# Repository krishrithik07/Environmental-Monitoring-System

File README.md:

# Environmental Monitoring System

**ESP32-C3 | LoRa Communication | KiCad PCB Design**

## Project Overview

This project focuses on designing an IoT-based Environmental Monitoring System using an ESP32-C3 microcontroller and LoRa communication.

The system integrates multiple sensors to monitor environmental conditions, including gas leakage, temperature and flame detection.

## Hardware Components

| Component | Purpose |
|---|---|
| ESP32-C3 | Main Controller |
| LoRa RA-02 | Wireless Communication |
| MQ-2 | Gas Detection |
| MQ-4 | Methane Detection |
| MQ-7 | Carbon Monoxide Detection |
| Temperature Sensor | Temperature Monitoring |
| Flame Sensor | Flame Detection |
| LM2576T-5.0 | 5V Power Regulation |
| LM2576T-3.3 | 3.3V Power Regulation |

## Design Tools

- KiCad – Schematic Capture and PCB Design
- ESP32-C3 – Embedded Controller
- LoRa – Wireless Communication

## Project Architecture

The system consists of a main controller and multiple sensor nodes. Sensor data is collected and communicated wirelessly through LoRa.

## Design Progress

- [ ] Component selection
- [ ] Schematic design
- [ ] Electrical Rule Check (ERC)
- [ ] PCB footprint assignment
- [ ] PCB layout
- [ ] Design Rule Check (DRC)
- [ ] Gerber generation
- [ ] PCB fabrication and testing

## Repository Structure

- `Schematic/` – KiCad schematic files
- `PCB_Layout/` – PCB design files
- `Libraries/` – Custom symbols and footprints
- `Datasheets/` – Component datasheets
- `BOM/` – Bill of Materials
- `Manufacturing/` – Manufacturing output files

## Author

**Krishna Raj M**

Electronics and Communication Engineering

**Project Category:** Embedded Systems | IoT | PCB Design

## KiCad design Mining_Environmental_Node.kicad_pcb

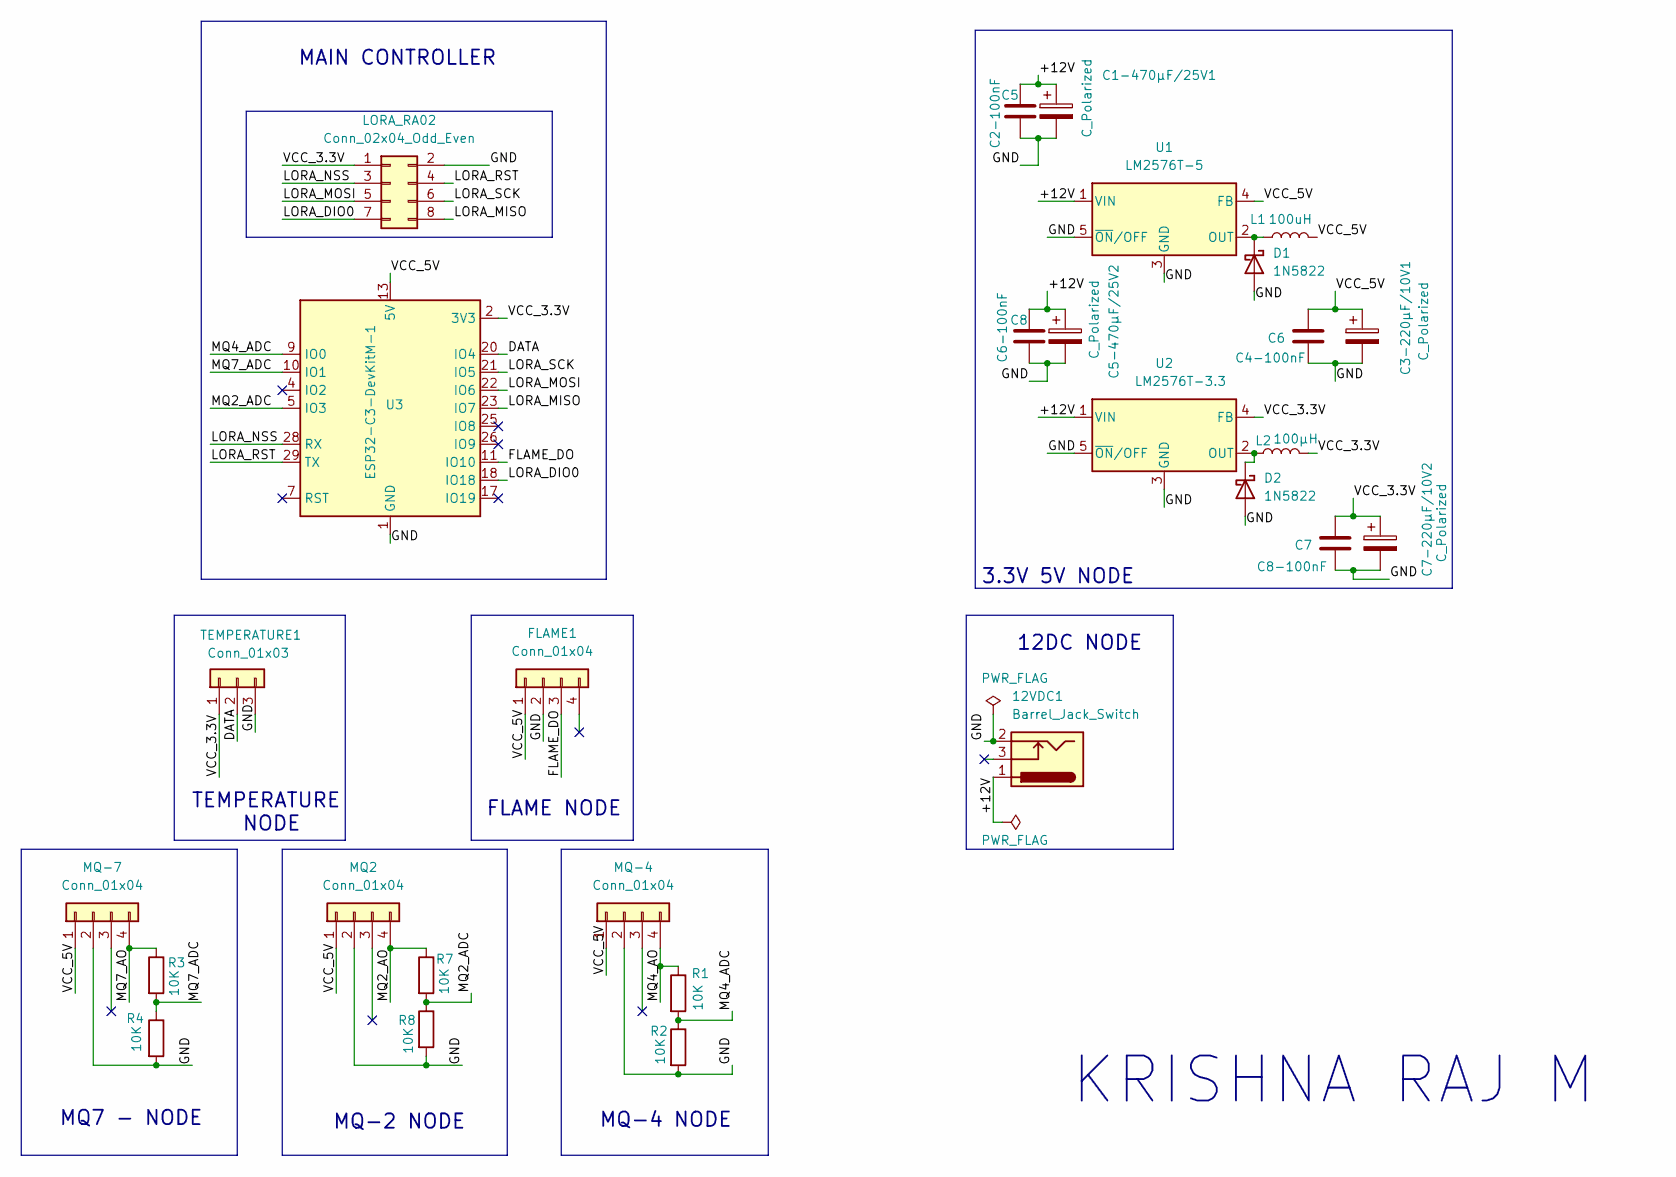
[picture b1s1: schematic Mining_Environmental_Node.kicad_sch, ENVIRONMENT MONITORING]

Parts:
12VDC1: Barrel_Jack_Switch; BarrelJack_Horizontal
C1-470µF/25V1, C3-220µF/10V1, C5-470µF/25V2, C7-220µF/10V2: C_Polarized; CP_Radial_D8.0mm_P3.50mm
C5: C2-100nF; C_Disc_D5.0mm_W2.5mm_P5.00mm
C6: C4-100nF; C_Disc_D5.0mm_W2.5mm_P5.00mm
C7: C8-100nF; C_Disc_D5.0mm_W2.5mm_P5.00mm
C8: C6-100nF; C_Disc_D5.0mm_W2.5mm_P5.00mm
D1, D2: 1N5822; D_DO-201AD_P15.24mm_Horizontal
FLAME1: Conn_01x04; PinSocket_1x04_P2.54mm_Vertical
L1: 100uH; L_Radial_D10.0mm_P5.00mm_Fastron_07M
L2: 100µH; L_Radial_D10.0mm_P5.00mm_Fastron_07M
LORA_RA02: Conn_02x04_Odd_Even; PinSocket_2x04_P2.54mm_Vertical
MQ2: Conn_01x04; PinSocket_1x04_P2.54mm_Vertical
MQ-4, MQ-7: Conn_01x04; PinSocket_1x04_P2.54mm_Vertical
R1, R2, R3, R4, R7, R8: 10K; R_Axial_DIN0207_L6.3mm_D2.5mm_P10.16mm_Horizontal
TEMPERATURE1: Conn_01x03; PinSocket_1x03_P2.54mm_Vertical
U1: LM2576T-5; TO-220-5_Vertical
U2: LM2576T-3.3; TO-220-5_Vertical
U3: ESP32-C3-DevKitM-1

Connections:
/+12V: 12VDC1.1, C1-470µF/25V1.1, C5.1, C5-470µF/25V2.1, C8.1, U1.1 (VIN), U2.1 (VIN)
/DATA: TEMPERATURE1.2, U3.20 (IO4)
/FLAME_DO: FLAME1.3, U3.11 (IO10)
/GND: 12VDC1.2, C1-470µF/25V1.2, C3-220µF/10V1.2, C5.2, C5-470µF/25V2.2, C6.2, C7.2, C7-220µF/10V2.2, C8.2, D1.2 (A), D2.2 (A), FLAME1.2, LORA_RA02.2, MQ2.2, MQ-4.2, MQ-7.2, R2.2, R4.2, R8.2, TEMPERATURE1.3, U1.3 (GND), U1.5 (~ON/OFF), U2.3 (GND), U2.5 (~ON/OFF), U3.1 (GND), U3.6 (GND), U3.8 (GND), U3.12 (GND), U3.15 (GND), U3.16 (GND), U3.19 (GND), U3.24 (GND), U3.27 (GND), U3.30 (GND)
/LORA_DIO0: LORA_RA02.7, U3.18 (IO18)
/LORA_MISO: LORA_RA02.8, U3.23 (IO7)
/LORA_MOSI: LORA_RA02.5, U3.22 (IO6)
/LORA_NSS: LORA_RA02.3, U3.28 (RX)
/LORA_RST: LORA_RA02.4, U3.29 (TX)
/LORA_SCK: LORA_RA02.6, U3.21 (IO5)
/MQ2_ADC: R7.2, R8.1, U3.5 (IO3)
/MQ2_AO: MQ2.4, R7.1
/MQ4_ADC: R1.2, R2.1, U3.9 (IO0)
/MQ4_AO: MQ-4.4, R1.1
/MQ7_ADC: R3.2, R4.1, U3.10 (IO1)
/MQ7_AO: MQ-7.4, R3.1
/VCC_3.3V: C7.1, C7-220µF/10V2.1, L2.2, LORA_RA02.1, TEMPERATURE1.1, U2.4 (FB), U3.2 (3V3), U3.3 (3V3)
/VCC_5V: C3-220µF/10V1.1, C6.1, FLAME1.1, L1.2, MQ2.1, MQ-4.1, MQ-7.1, U1.4 (FB), U3.13 (5V), U3.14 (5V)
unnamed: D1.1 (K), L1.1, U1.2 (OUT)
unnamed: D2.1 (K), L2.1, U2.2 (OUT)

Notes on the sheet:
KRISHNA RAJ M
3.3V 5V NODE
TEMPERATURE NODE
MAIN CONTROLLER
12DC NODE
FLAME NODE
MQ-4 NODE
MQ7 - NODE
MQ-2 NODE

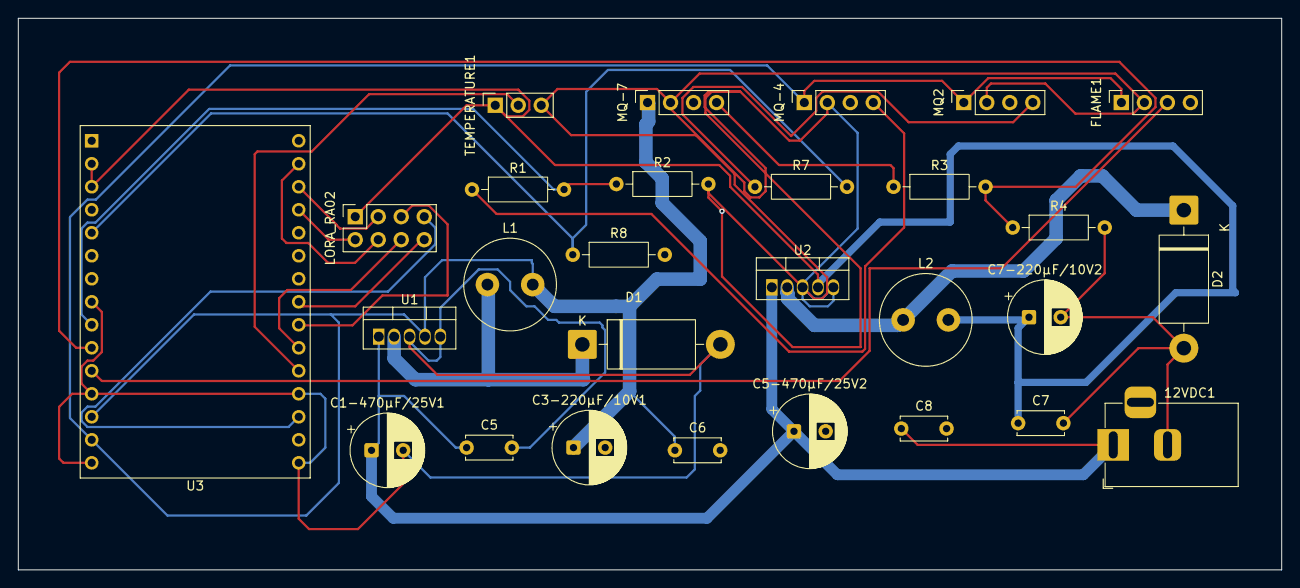
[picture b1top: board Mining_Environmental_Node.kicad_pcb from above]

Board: 2 copper layers, 139.5 x 60.9 mm, 28 parts (0 on the bottom side), 20 nets.
